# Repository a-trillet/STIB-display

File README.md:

# Brussels transport lines Display

## What you need
- ESP32 devkit (we used esp32 WROOM devkit1)
- 16 channel MUX (for maximum 16 LEDs)
- basic electronic componenents (leds, resistor, test board or PCB...)  

(Not yet ready !)
For a complete list of electronic components and the references we used, refer to [hardware section](./hardware/).   
In the same section, the PCB kicad files can be downloaded and you can order them through any PCB manufacturer. 

## Getting started with the STIB API
- Create an account on https://data.stib-mivb.brussels/pages/home/
- Generate API key on https://data.stib-mivb.brussels/account/api-keys/
- Test the api with [request.py](./pc-test/request.py)
    - Change the ****  in the request header with the generated API key
    - Running `python request.py` will show buses location on line 71, you will want to adapt stop IDs to the line you are interested in. You can get all stop IDs for all lines using the WEB API for stops information:  [stops-by-line-production](https://data.stib-mivb.brussels/explore/dataset/stops-by-line-production/api/)

## Getting started on ESP 32
The following steps and requirements are provided for Windows.
- Download the latest micropython firmware for esp32 here : [micropython firmware](https://micropython.org/download/ESP32_GENERIC/)
- Download useful python tools: 
    - `pip install esptool`
    - `pip install adafruit-ampy`
- Erase flash of ESP: `python -m esptool --chip esp32 erase_flash`
- Flash ESP with micropython firmware: `python -m esptool --chip esp32 --port COMX write_flash -z 0x1000 ESP32_GENERIC-20241129-v1.24.1.bin`
- Adpat **** in main.py with your API key and Wifi credentials
- Send main.py to the ESP to be executed automatically: `<path\to\ampy.exe> --port COMX put <path\to\main.py>`
- Get buses position through serial communication (using Putty per example)
```
LED 3 activée
Bus à: 3559 - ULB vers Jeanne 3559
LED 5 activée
Bus à: 2397 - Buyl(delta) vers ULB 2397
LED 3 activée
Bus à: 3525 - Jeanne vers Buyl 3525
LED 4 activée
```

Like us, you might need to: 
- Download the CP210x driver for ESP USB to UART bridge: [download CP210x](https://www.silabs.com/developer-tools/usb-to-uart-bridge-vcp-drivers?tab=downloads)
- Change the baudrate for the discovered device in device manager to **115200**
- Don't forget to close putty before writing to it

Get more detailed steps: https://docs.micropython.org/en/latest/esp32/tutorial/intro.html  

## Make it ! 
Instructions, schematics and PCBs layout can be found under [hardware section](./hardware/). 

And in the code you will have to adapt the list of stops you want to see with the stop IDs available on STIB web API. Also you will have to change the channel number of each led that has to turn on in the dictionnary with bus stops. (currently only one MUX). 

## CC License 
All work in this project is openly licensed via [CC BY-NC 4.0](https://creativecommons.org/licenses/by-nc/4.0/).

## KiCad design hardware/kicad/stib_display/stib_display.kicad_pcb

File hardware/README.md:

# PCB layout
Helpful ressources for kicad V8,: [Kicad 8 - Getting Started](https://docs.kicad.org/8.0/en/getting_started_in_kicad/getting_started_in_kicad.html)

PCB can easily be manufactured at any PCB manufacturer. I ordered mine at JCLPCB by uploading the gerber and drill files for each board.   
I had to regenerate those with one board only at a time (deleting the rest on the pcb layout). 

The idea is to solder the LED boards in serie, one per line wanted in the final design: 
- J6 Pins of the ESP32 board (Trillet 1.1) go to IN pin of first LED board (Trillet 1.2)
- Pins OUT of the first LED board go to IN pin of the next LED board
## BOM 
### LED board
|Amount|Component|Ref number|
|-|-|-|
| 1 | 3.3v linear voltage regulator | [AMS1117-3.3V](https://www.alldatasheet.com/datasheet-pdf/pdf/205691/ADMOS/AMS1117-3.3.html) |
| 2 | 100nF SMD Capacitor | 100nF 1206 SMD:C |
| 2 | 22uF SMD Capacitor | 22uF 1206 SMD:C |
| 2 | 8bit shift register | [SN74HC595N (THT) ](https://www.alldatasheet.fr/datasheet-pdf/download/27939/TI/SN74HC595N.html) |
| 12 | LED THT | 5mm THT LED|
| 12 | Resistor THT (see value below)| DIN 0204 R THT 3.6 mm |
| 1 | 7  pin JST connector (female + male + cable) | [2.54 mm JST male/ + female](https://fr.aliexpress.com/item/32964549472.html)  |

### ESP 32 - Power board
|Amount|Component|Ref number|
|-|-|-|
| 1 | Terminal copnnector block 5mm - 2Pin | [ZR301-2P-Green-50](https://fr.aliexpress.com/item/1005007055503766.html) |
| 5 | 10 k Ohm  Resistor | 10k Ohm - DIN 0204 R THT 3.6 mm|
| 1 | 3.5 A SMD fuse | [3.5A 1206 SMD:Fuse](https://fr.aliexpress.com/item/32901034711.html) |
| 2 | ESP 32 Wroom-32 Nodemcu type C | [esp32 devkit  (check pinout!)](https://fr.aliexpress.com/item/1005006478818552.html) |
| 1 | 100nF THT polarized electrolitic capacitor | 5mm THT:C |
| 1 | 100uF THT polarized electrolitic capacitor | 5mm THT:C |
| 1 | 7  pin JST connector (female + male + cable) | [2.54 mm JST male/ + female](https://fr.aliexpress.com/item/32964549472.html)  |

## LED to Resitor value

TODO

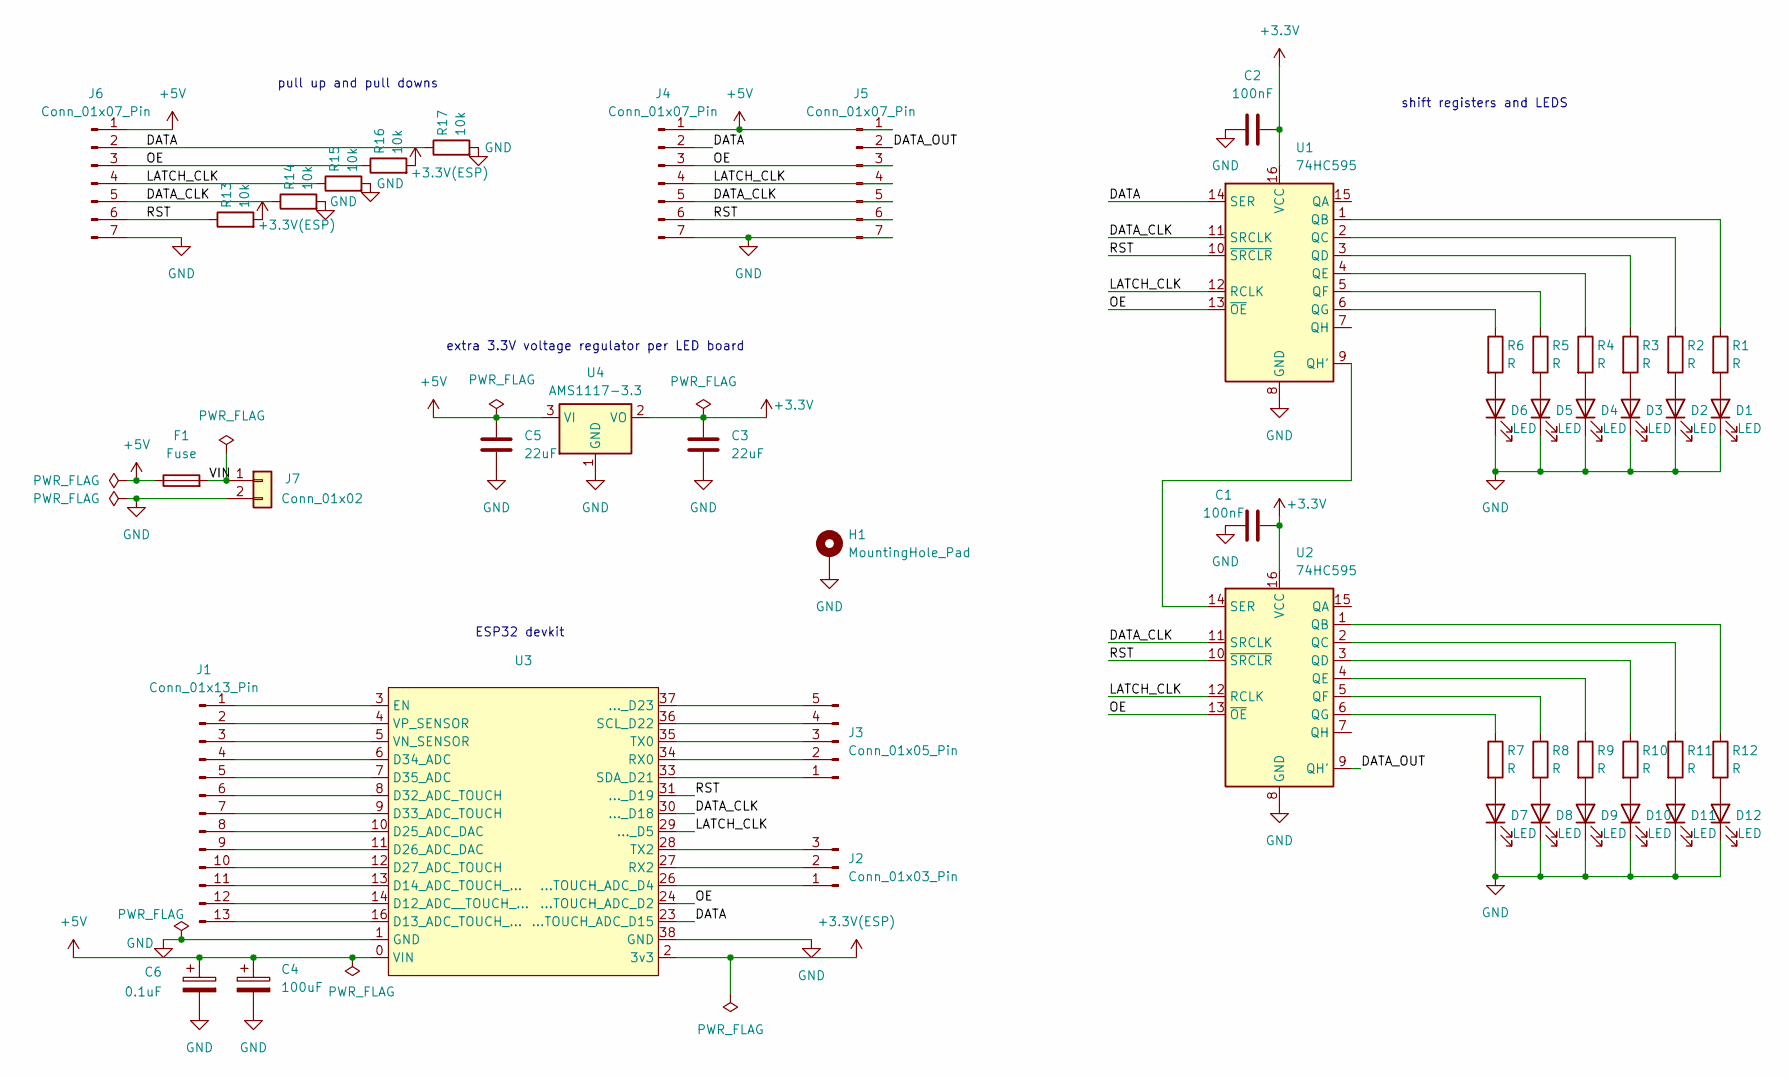
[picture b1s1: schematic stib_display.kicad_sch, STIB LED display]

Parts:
C1, C2: 100nF; C_1206_3216Metric_Pad1.33x1.80mm_HandSolder
C3, C5: 22uF; C_1206_3216Metric_Pad1.33x1.80mm_HandSolder
C4: 100uF; C_Radial_D5.0mm_H11.0mm_P2.00mm
C6: 0.1uF; C_Radial_D5.0mm_H11.0mm_P2.00mm
D1, D2, D3, D4, D5, D6, D7, D8, D9, D10, D11, D12: LED; LED_D5.0mm
F1: Fuse; Fuse_1206_3216Metric_Pad1.42x1.75mm_HandSolder
H1: MountingHole_Pad; MountingHole_2.7mm_M2.5_DIN965_Pad_TopBottom
J1: Conn_01x13_Pin; PinSocket_1x13_P2.54mm_Vertical
J2: Conn_01x03_Pin; PinHeader_1x03_P2.54mm_Vertical
J3: Conn_01x05_Pin; PinSocket_1x05_P2.54mm_Vertical
J4, J5, J6: Conn_01x07_Pin; PinSocket_1x07_P2.54mm_Vertical
J7: Conn_01x02; TerminalBlock_Phoenix_MKDS-1,5-2_1x02_P5.00mm_Horizontal
R1, R2, R3, R4, R5, R6, R7, R8, R9, R10, R11, R12: R; R_Axial_DIN0204_L3.6mm_D1.6mm_P7.62mm_Horizontal
R13, R14, R15, R16, R17: 10k; R_Axial_DIN0204_L3.6mm_D1.6mm_P7.62mm_Horizontal
U1, U2: 74HC595; DIP-16_W7.62mm_LongPads
U3: ESP32_Nodemcu_devkit
U4: AMS1117-3.3; SOT-223-3_TabPin2

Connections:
+3.3V: C1.2, C2.2, C3.1, U1.16 (VCC), U2.16 (VCC), U4.2 (VO)
+3.3V(ESP): R13.2, R16.2, U3.2 (3v3)
+5V: C4.1, C5.1, C6.1, F1.1, J4.1, J5.1, J6.1, U3.0 (VIN), U4.3 (VI)
/DATA: J4.2, J6.2, R17.1, U1.14 (SER), U3.23 (...TOUCH_ADC_D15)
/DATA_CLK: J4.5, J5.5, J6.5, R14.1, U1.11 (SRCLK), U2.11 (SRCLK), U3.30 (..._D18)
/DATA_OUT: J5.2, U2.9 (QH')
/LATCH_CLK: J4.4, J5.4, J6.4, R15.1, U1.12 (RCLK), U2.12 (RCLK), U3.29 (..._D5)
/OE: J4.3, J5.3, J6.3, R16.1, U1.13 (~OE), U2.13 (~OE), U3.24 (...TOUCH_ADC_D2)
/RST: J4.6, J5.6, J6.6, R13.1, U1.10 (~SRCLR), U2.10 (~SRCLR), U3.31 (..._D19)
/VIN: F1.2, J7.1
GND: C1.1, C2.1, C3.2, C4.2, C5.2, C6.2, D1.1 (K), D2.1 (K), D3.1 (K), D4.1 (K), D5.1 (K), D6.1 (K), D7.1 (K), D8.1 (K), D9.1 (K), D10.1 (K), D11.1 (K), D12.1 (K), H1.1, J4.7, J5.7, J6.7, J7.2, R14.2, R15.2, R17.2, U1.8 (GND), U2.8 (GND), U3.1 (GND), U3.38 (GND), U4.1 (GND)
unnamed: D1.2 (A), R1.2
unnamed: D2.2 (A), R2.2
unnamed: D3.2 (A), R3.2
unnamed: D4.2 (A), R4.2
unnamed: D5.2 (A), R5.2
unnamed: D6.2 (A), R6.2
unnamed: D7.2 (A), R7.2
unnamed: D8.2 (A), R8.2
unnamed: D9.2 (A), R9.2
unnamed: D10.2 (A), R10.2
unnamed: D11.2 (A), R11.2
unnamed: D12.2 (A), R12.2
unnamed: J1.1, U3.3 (EN)
unnamed: J1.2, U3.4 (VP_SENSOR)
unnamed: J1.3, U3.5 (VN_SENSOR)
unnamed: J1.4, U3.6 (D34_ADC)
unnamed: J1.5, U3.7 (D35_ADC)
unnamed: J1.6, U3.8 (D32_ADC_TOUCH)
unnamed: J1.7, U3.9 (D33_ADC_TOUCH)
unnamed: J1.8, U3.10 (D25_ADC_DAC)
unnamed: J1.9, U3.11 (D26_ADC_DAC)
unnamed: J1.10, U3.12 (D27_ADC_TOUCH)
unnamed: J1.11, U3.13 (D14_ADC_TOUCH_...)
unnamed: J1.12, U3.14 (D12_ADC__TOUCH_...)
unnamed: J1.13, U3.16 (D13_ADC_TOUCH_...)
unnamed: J2.1, U3.26 (...TOUCH_ADC_D4)
unnamed: J2.2, U3.27 (RX2)
unnamed: J2.3, U3.28 (TX2)
unnamed: J3.1, U3.33 (SDA_D21)
unnamed: J3.2, U3.34 (RX0)
unnamed: J3.3, U3.35 (TX0)
unnamed: J3.4, U3.36 (SCL_D22)
unnamed: J3.5, U3.37 (..._D23)
unnamed: R1.1, U1.1 (QB)
unnamed: R2.1, U1.2 (QC)
unnamed: R3.1, U1.3 (QD)
unnamed: R4.1, U1.4 (QE)
unnamed: R5.1, U1.5 (QF)
unnamed: R6.1, U1.6 (QG)
unnamed: U1.9 (QH'), U2.14 (SER)
unnamed: R12.1, U2.1 (QB)
unnamed: R11.1, U2.2 (QC)
unnamed: R10.1, U2.3 (QD)
unnamed: R9.1, U2.4 (QE)
unnamed: R8.1, U2.5 (QF)
unnamed: R7.1, U2.6 (QG)

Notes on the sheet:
pull up and pull downs
shift registers and LEDS
extra 3.3V voltage regulator per LED board
ESP32 devkit

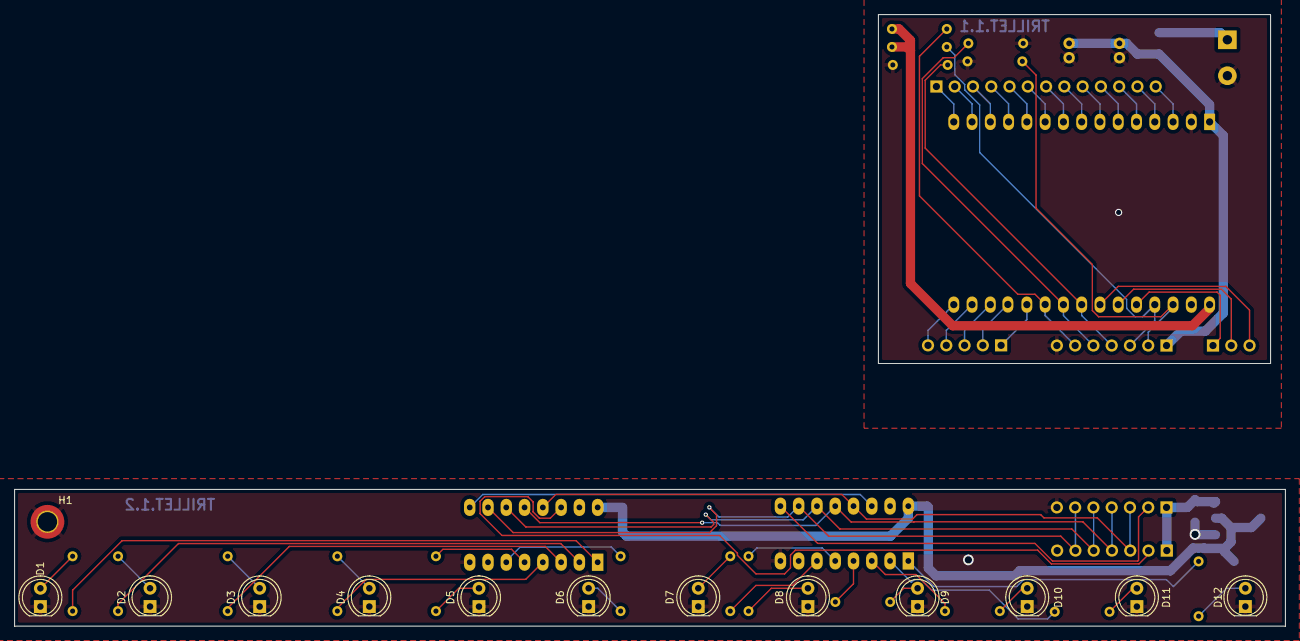
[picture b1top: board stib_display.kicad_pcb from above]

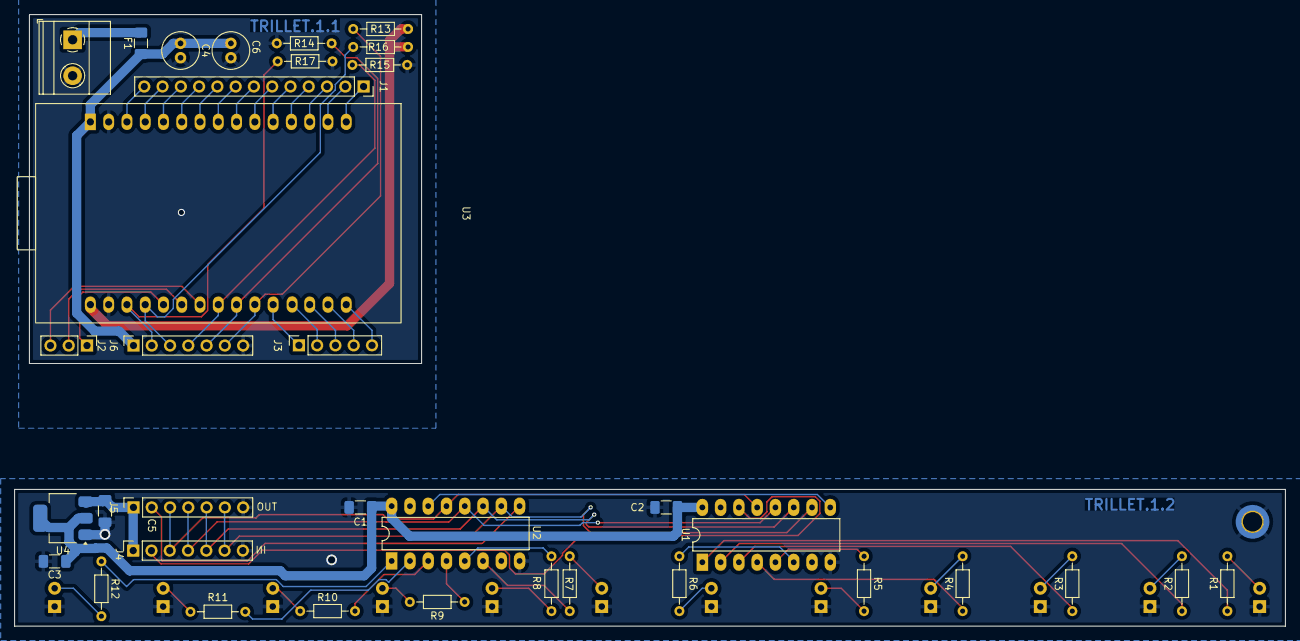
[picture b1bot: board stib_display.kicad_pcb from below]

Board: 2 copper layers, 176.6 x 85.0 mm, 48 parts (35 on the bottom side), 57 nets.

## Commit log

2024-12-31 Initial commit for working proto
2025-03-10 new board based on shift registers + kicad files + BOMs
2025-08-10 new version of upython code
2025-08-13 cpp conversion attempt by claude
2025-08-14 storage for wifi pass
2025-08-14 working wifi save
2025-08-15 new partiotioning for ota
2025-08-15 working tls no check in menuconfig
2025-08-16 working led updater, first attempt for updater
2025-08-16 ota_manager debugging
2025-08-16 working updater but slow
2025-08-16 fully working and fast ota updater
